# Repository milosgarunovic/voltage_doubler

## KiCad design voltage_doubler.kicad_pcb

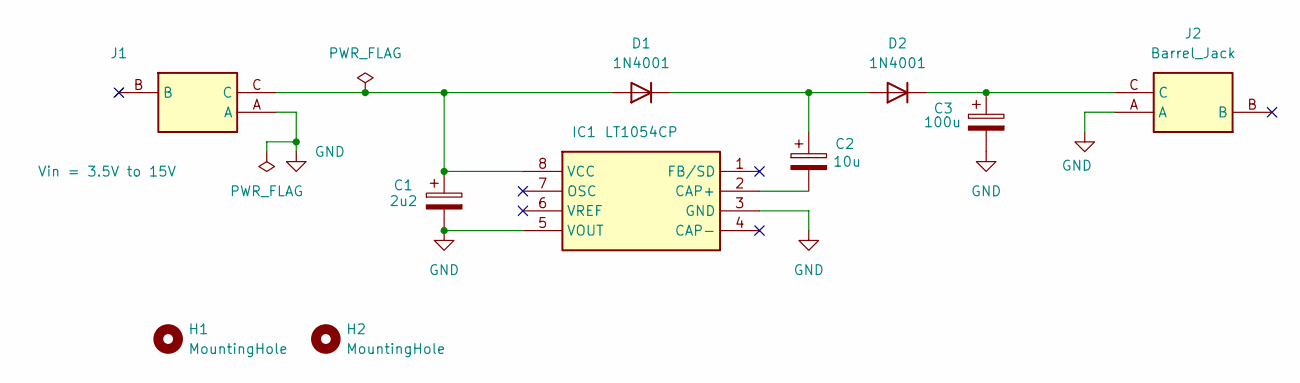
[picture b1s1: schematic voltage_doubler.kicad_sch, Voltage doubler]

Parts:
C1: 2u2; CP_Radial_D8.0mm_P2.50mm
C2: 10u; CP_Radial_D5.0mm_P2.50mm
C3: 100u; CP_Radial_D8.0mm_P2.50mm
D1, D2: 1N4001; D_5W_P10.16mm_Horizontal
H1, H2: MountingHole; MountingHole_3mm
IC1: LT1054CP; Mouser Part Number 595-LT1054CP
J1: Vin = 3.5V to 15V; 163179PHEX; Mouser Part Number 163-179PH-EX
J2: Barrel_Jack; 163179PHEX; Mouser Part Number 163-179PH-EX

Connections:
GND: C1.2, C3.2, IC1.3 (GND), IC1.5 (VOUT), J1.A, J2.A
unnamed: C1.1, D1.2 (A), IC1.8 (VCC), J1.C
unnamed: C2.1, D1.1 (K), D2.2 (A)
unnamed: C3.1, D2.1 (K), J2.C
unnamed: C2.2, IC1.2 (CAP+)

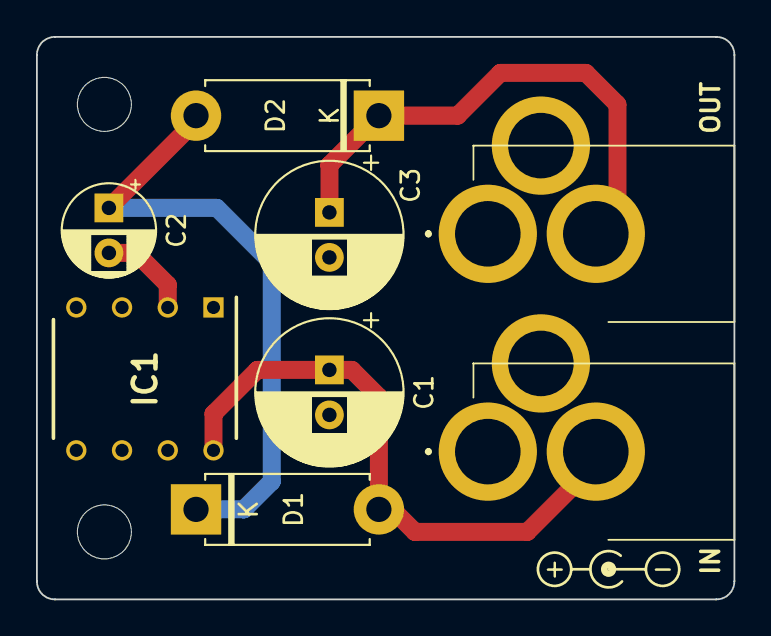
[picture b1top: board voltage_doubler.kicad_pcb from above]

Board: 2 copper layers, 38.8 x 31.2 mm, 10 parts (0 on the bottom side), 5 nets.

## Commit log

2025-03-09 add .gitignore
2025-03-09 update checklist, add graphics, add date variable
2025-03-09 update checklist
